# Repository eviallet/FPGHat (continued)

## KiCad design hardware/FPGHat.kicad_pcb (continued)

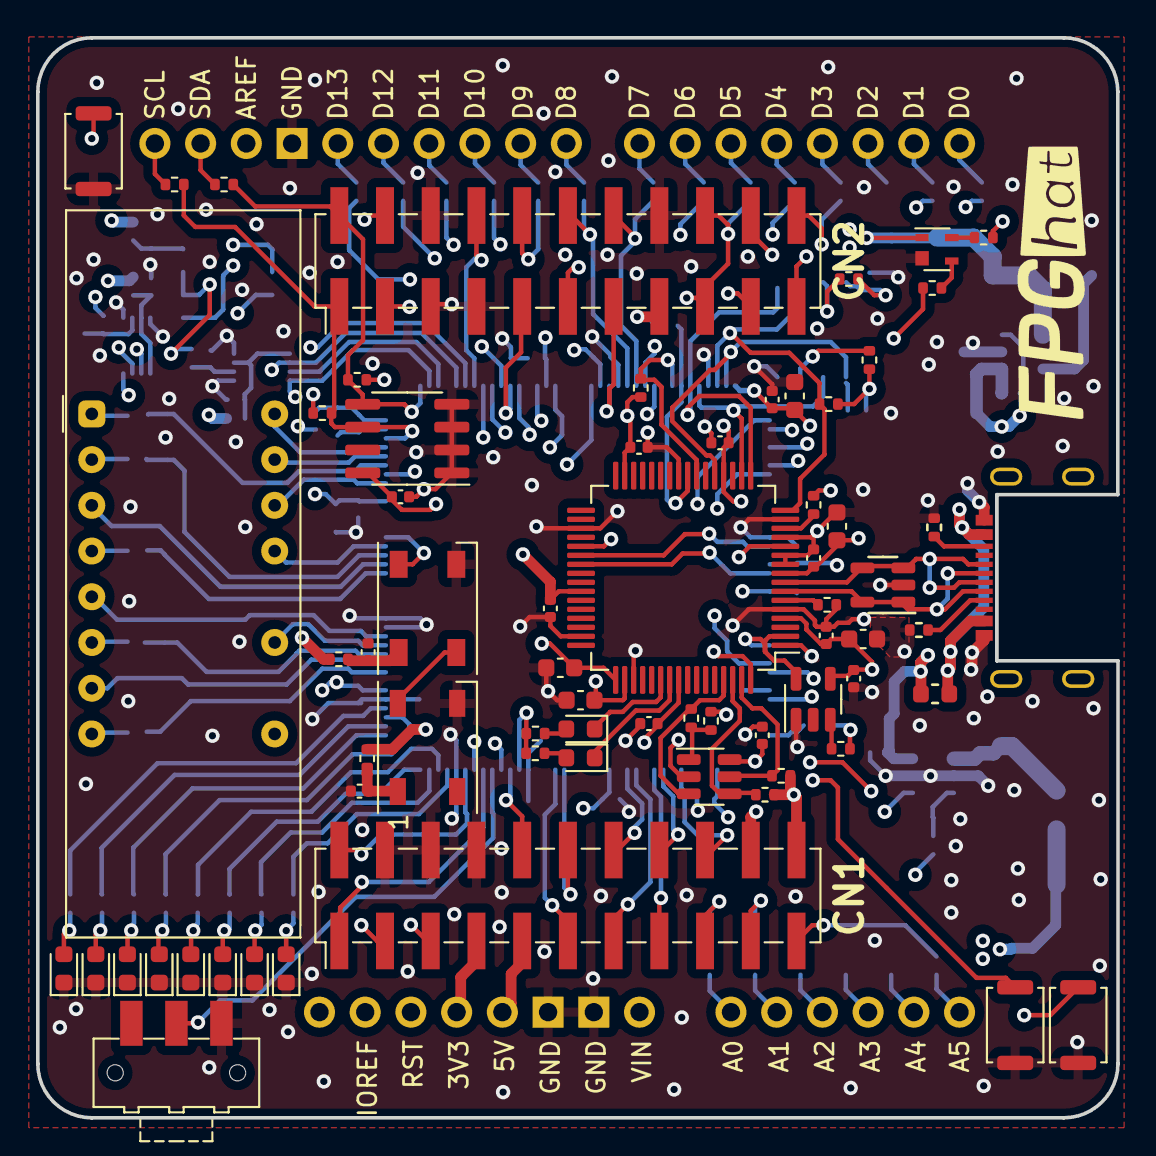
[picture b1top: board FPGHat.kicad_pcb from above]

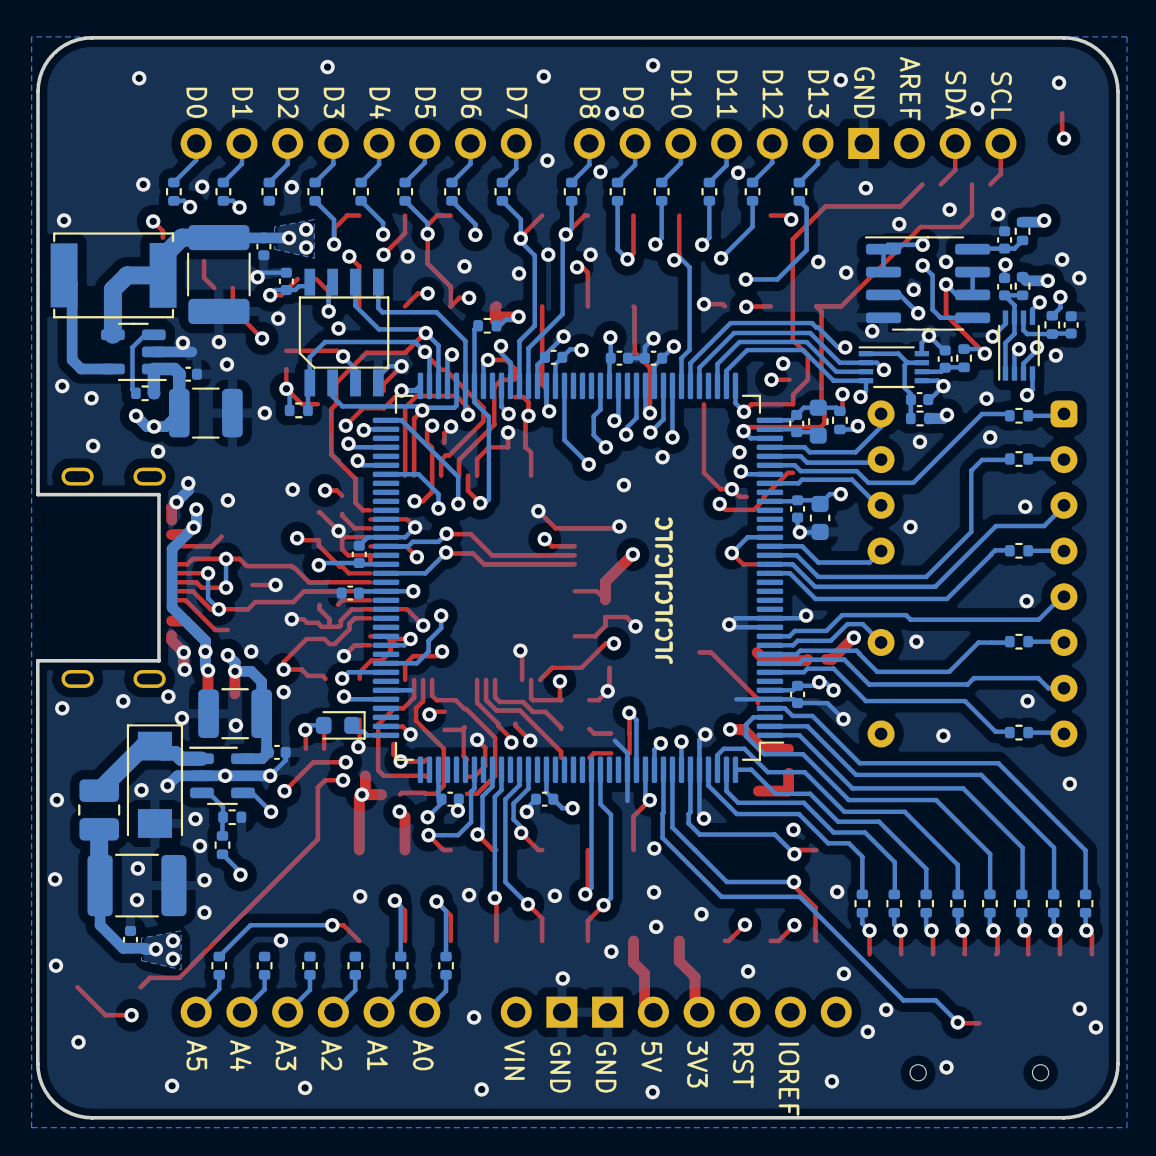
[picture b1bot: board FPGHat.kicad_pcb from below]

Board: 4 copper layers, 60.0 x 60.0 mm, 149 parts (81 on the bottom side), 157 nets.

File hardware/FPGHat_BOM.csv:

Reference, Quantity, Value, Footprint, Datasheet, Price, Store Ref, Stock, Tolerance
C1 C2 C7 C8 C9 C10 C11 C12 C13 C15 C17 C19 C21 C22 C23 C24 C25 C27 C28 C30 C32 C33 C34 C35 C36 C37 C38 C39 C42 C43 ,30,"100n","Capacitor_SMD:C_0402_1005Metric","","0,02","963-EMK105BJ104KVHF","",""
C14 ,1,"2.2u","Capacitor_SMD:C_1210_3225Metric","","0,49","80-C1210C225K4R","",""
C16 C20 ,2,"10u","Capacitor_SMD:C_1812_4532Metric","","1,26","581-1812YC106KAT2A","",""
C18 ,1,"4.7u","Capacitor_SMD:C_1210_3225Metric","","0,76"," 80-C1210C475K4RAUTO","",""
C26 C29 ,2,"1u","Capacitor_SMD:C_0603_1608Metric","","0","603-CC603ZRY5V7BB105","8",""
C3 C4 C5 C6 ,4,"4.7u","Capacitor_SMD:C_0603_1608Metric","","0","","",""
C31 ,1,"10u","Capacitor_SMD:C_0603_1608Metric",""
C40 C41 ,2,"1n","Capacitor_SMD:C_0402_1005Metric","","0","581-0402ZD102KAT2A","10",""
D1 D3 D4 D5 D6 D7 D8 ,7,"green","LED_SMD:LED_0603_1608Metric","","0,33","755-SML-D12P8WT86C ","",""
D11 D14 ,2,"WS2812B","LED_SMD:LED_WS2812B_PLCC4_5.0x5.0mm_P3.2mm","https://cdn-shop.adafruit.com/datasheets/WS2812B.pdf","0","","10",""
D12 ,1,"SS14FL-TP","Arduino shields:DO-221AC-2","","0,4","833-SS14FL-TP","",""
D13 ,1,"CDBU0520","Diode_SMD:D_0603_1608Metric","","0,43","750-CDBU0520","",""
D2 D9 D10 ,3,"orange","LED_SMD:LED_0603_1608Metric","","0,33","755-SML-D12P8WT86C ","",""
F1 ,1,"750m","Fuse:Fuse_0603_1608Metric","","0,38","504-CC06FA750MA-TR ","",""
J1 ,1,"USB_C_Receptacle_USB2.0","gueg_lib:USB_C_Molex_216990-0002","https://www.molex.com/pdm_docs/sd/2169900002_sd.pdf","0","538-216990-0002 ","1",""
J2 J3 ,2,"Conn_02x11_Odd_Even","gueg_lib:PinHeader_2x11_P2.54mm_Vertical_SMD","","3,6"," 200-TSM11102LDV ","",""
L1 ,1,"LQM2HPN3R3MG0L","Inductor_SMD:L_1008_2520Metric","","0,23","81-LQM2HPN3R3MG0L","",""
L2 ,1,"10u","gueg_lib:L_Coilcraft_D01608C","","1,86","994-DO1608C-103MLC","",""
R1 R2 ,2,"5.1k","Resistor_SMD:R_0402_1005Metric","","0,09","667-ERJ-2RKF5101X ","",""
R10 R11 ,2,"330","Resistor_SMD:R_0402_1005Metric","","0","603-RC0402JR-13330RL","9",""
R16 R20 R21 R33 R34 R35 R36 R37 R38 R39 R40 R41 R42 R43 R44 R45 R46 R47 R48 R49 R50 R51 R52 R53 R61 R62 R63 R66 R67 ,29,"0","Resistor_SMD:R_0402_1005Metric","","0","652-CR0402AJ/-000GAS","86",""
R17 ,1,"44.8k","Resistor_SMD:R_0402_1005Metric","","0,36","603-RT0402BRD0744K8L","","0.1%"
R24 R25 R26 R27 R28 R29 R30 R31 ,8,"1k","Resistor_SMD:R_0402_1005Metric","","0","603-RT0402FRE071KL","8",""
R3 R4 ,2,"2.2k","Resistor_SMD:R_0402_1005Metric","","0,1","603-RC0402JR-7D2K2L","",""
R5 R6 R7 R8 R12 R13 R14 R15 R18 R19 R22 R23 R54 R55 ,14,"10k","Resistor_SMD:R_0402_1005Metric","","0,014","603-RC0402JR-7D10KL","",""
R56 R57 R58 R59 R60 ,5,"240","Resistor_SMD:R_0402_1005Metric","","0,07","603-RT0402FRE07240RL","",""
R32 R64 R65 ,3,"100","Resistor_SMD:R_0402_1005Metric","","0,11","652-CRT0402FZ1000GLF","",""
R9 ,1,"12k","Resistor_SMD:R_0402_1005Metric","","0","603-RT0402BRD0712K4L","2","0.1%"
SW1 ,1,"SW_SPDT","Button_Switch_SMD:SW_SPDT_CK-JS102011SAQN","","0,66","611-JS102011SAQN","",""
SW2 SW3 SW4 ,3,"SW_Push","gueg_lib:SW_Push_SPST_NO_Alps_SKRK","","0,82","688-SKRKAG","",""
U1 ,1,"ESDS312DBVR","Package_TO_SOT_SMD:SOT-23-5","","0,58","595-ESDS312DBVR","",""
U11 ,1,"LTC-4627JR","Display_7Segment:LTC-4627Jx","http://optoelectronics.liteon.com/upload/download/DS30-2000-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","2,26","859-LTC-4627JR","",""
U12 ,1,"LMR10515XMF","Package_TO_SOT_SMD:SOT-23-5","http://www.ti.com/lit/ds/symlink/lmr10515.pdf","0","","1",""
U13 ,1,"LM3670MF","Package_TO_SOT_SMD:TSOT-23-5","http://www.ti.com/lit/ds/symlink/lm3670.pdf","1,31","926-LM3670MFX12NOPB","",""
U14 ,1,"ADCMP356","Package_TO_SOT_SMD:Analog_KS-4","https://www.analog.com/media/en/technical-documentation/data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","1,24","584-ADCMP356YKSZR7","",""
U2 ,1,"93C56BT-E/OT","Package_TO_SOT_SMD:SOT-23-6","https://www.mouser.fr/datasheet/2/268/21794b-74044.pdf","0,38","579-93C56BT-E/OT","",""
U3 ,1,"SiT2001BI-S2-33E","Package_TO_SOT_SMD:SOT-23-5","","1,52","788-2001BIS233E120G","",""
U4 ,1,"FT2232HL","Package_QFP:LQFP-64_10x10mm_P0.5mm","https://www.ftdichip.com/Support/Documents/DataSheets/ICs/DS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","6,38","895-FT2232HL","",""
U5 ,1,"N25Q032","gueg_lib:SOP2-8","https://www.mouser.fr/datasheet/2/12/Micron_Datasheet_N25Q03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","1,53","913-N25Q032A13ESC40F","",""
U6 ,1,"ICE40HX1K-TQ144","Package_QFP:TQFP-144_20x20mm_P0.5mm","http://www.latticesemi.com/Products/FPGAandCPLD/iCE40","7,68","842-ICE40HX1K-TQ144","",""
U7 ,1,"NV24C32LV","Package_SO:SOIC-8_3.9x4.9mm_P1.27mm","https://www.mouser.fr/datasheet/2/308/NV24C32LV_D-1628011.pdf","0,41","863-NV24C32DWVLT3G","",""
U8 ,1,"MCP662","Package_SO:SOIC-8_3.9x4.9mm_P1.27mm","https://www.mouser.fr/datasheet/2/268/20002194E-2448650.pdf","1,63","579-MCP662-E/SN","",""
U9 U10 ,2,"ADS7039","Package_SO:VSSOP-8_2.3x2mm_P0.5mm","http://www.ti.com/lit/ds/symlink/ads7039-q1.pdf","1,96","595-ADS7039QDCURQ1","",""
XA1 ,1,"Arduino_Uno_Shield","gueg_lib:Arduino_Uno_Custom_Hat","https://docs.arduino.cc/hardware/uno-rev3","0,8","200-TSW11007TS---QTY4","",""

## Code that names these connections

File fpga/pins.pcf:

# main fpga signals
set_io   -pullup yes    nrst        104
set_io                  rclk        98

# leds
set_io                  led0        141
set_io                  led1        143
set_io                  led2        144
set_io                  led3        142
set_io                  led4        3
set_io                  led5        1
set_io                  led6        2
set_io                  led7        4

# switches
set_io   -pullup yes    sw          136
set_io   -pullup yes    btn         101

# uart
set_io                  ftdi_rx     87
set_io                  ftdi_tx     90
set_io                  fpga_rx     76
set_io                  fpga_tx     78

# spi
set_io                  st_spi_sck  44
set_io                  st_spi_sdo  45
set_io                  st_spi_nss  50

# adc
set_io   -pullup yes    adc_ssn     38
set_io                  adc_clk     41
set_io                  adc1_sdo    42
set_io                  adc2_sdo    39

# segments
set_io                  seg_a0      19
set_io                  seg_a1      31
set_io                  seg_a2      21
set_io                  seg_a3      10
set_io                  seg_a4      8
set_io                  seg_k0      9
set_io                  seg_k1      29
set_io                  seg_k2      33
set_io                  seg_k3      22
set_io                  seg_k4      20
set_io                  seg_k5      12
set_io                  seg_k6      11
set_io                  seg_k7      32

# rgb
set_io                  rgb         23

# connectors
# cn1
set_io                  cn1_1       137
set_io                  cn1_2       139
set_io                  cn1_3       138
set_io                  cn1_5       135
set_io                  cn1_10      134
set_io                  cn1_11      129
set_io                  cn1_12      128
set_io                  cn1_13      120
set_io                  cn1_14      121
set_io                  cn1_15      118
set_io                  cn1_16      117
set_io                  cn1_18      115
# cn2
set_io                  cn2_8       43
set_io                  cn2_9       47
set_io                  cn2_11      56
set_io                  cn2_13      58
set_io                  cn2_19      73
set_io                  cn2_20      79
set_io                  cn2_21      74

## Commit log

2023-05-02 v0.1
2025-03-11 VHDL updated
